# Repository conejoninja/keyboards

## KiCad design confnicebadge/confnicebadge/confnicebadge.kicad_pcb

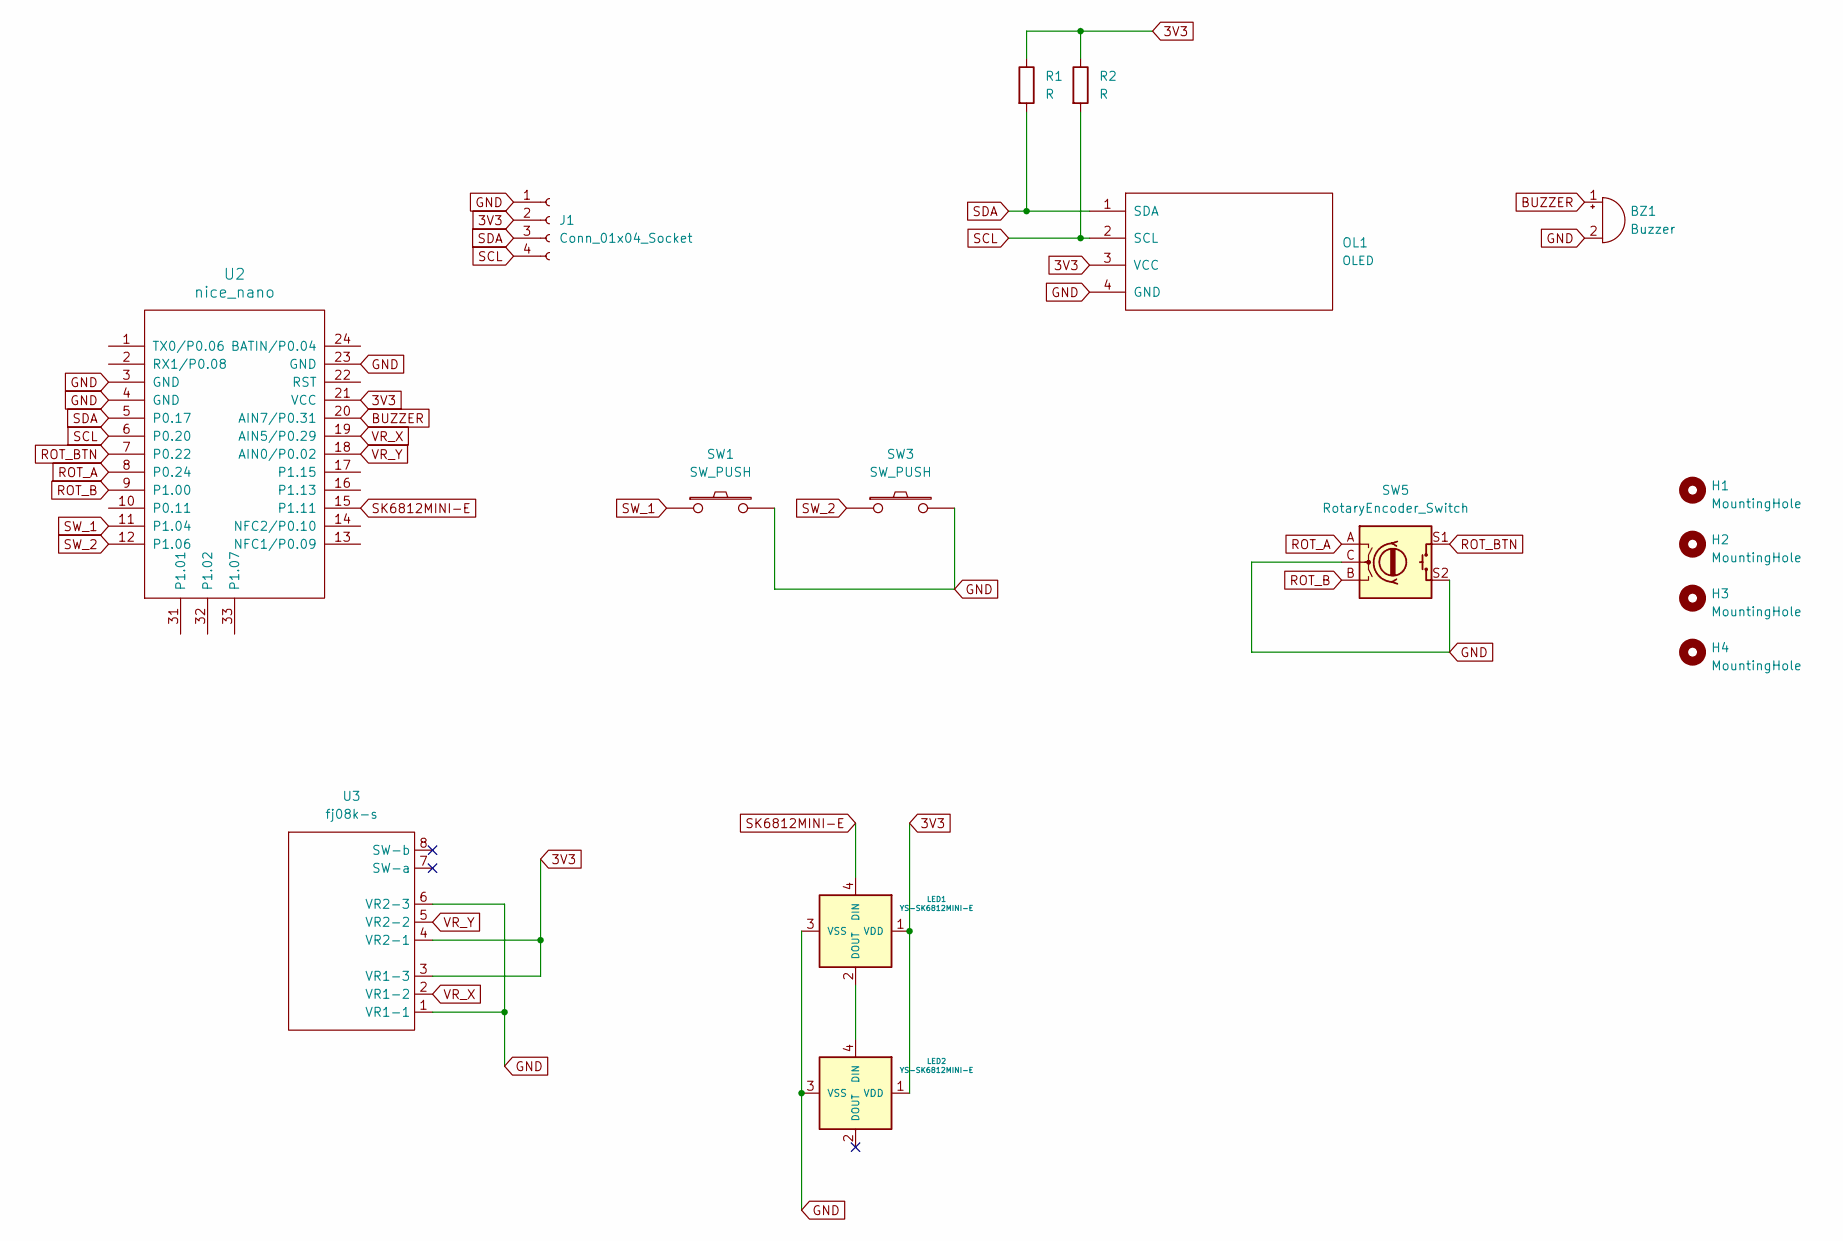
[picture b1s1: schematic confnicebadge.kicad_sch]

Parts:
BZ1: Buzzer; buzzer 5.5mm
H1, H2, H3, H4: MountingHole; M2_HOLE_v2
J1: Conn_01x04_Socket; PinHeader_1x04_P2.54mm_Vertical
LED1, LED2: YS-SK6812MINI-E
OL1: OLED
R1, R2: R; R_Axial_DIN0207_L6.3mm_D2.5mm_P10.16mm_Horizontal
SW1, SW3: SW_PUSH; CherryMX_Hotswap
SW5: RotaryEncoder_Switch; RotaryEncoder_Alps_EC11E-Switch_Vertical_H20mm
U2: nice_nano
U3: fj08k-s; FJ08K-S

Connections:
3V3: J1.2, LED1.1 (VDD), LED2.1 (VDD), OL1.3 (VCC), R1.1, R2.1, U2.21 (VCC), U3.3 (VR1-3), U3.4 (VR2-1)
BUZZER: BZ1.1 (+), U2.20 (AIN7/P0.31)
GND: BZ1.2 (-), J1.1, LED1.3 (VSS), LED2.3 (VSS), OL1.4 (GND), SW1.2, SW3.2, SW5.C, SW5.S2, U2.3 (GND), U2.4 (GND), U2.23 (GND), U3.1 (VR1-1), U3.6 (VR2-3)
unnamed: LED1.2 (DOUT), LED2.4 (DIN)
ROT_A: SW5.A, U2.8 (P0.24)
ROT_B: SW5.B, U2.9 (P1.00)
ROT_BTN: SW5.S1, U2.7 (P0.22)
SCL: J1.4, OL1.2 (SCL), R2.2, U2.6 (P0.20)
SDA: J1.3, OL1.1 (SDA), R1.2, U2.5 (P0.17)
SK6812MINI-E: LED1.4 (DIN), U2.15 (P1.11)
SW_1: SW1.1, U2.11 (P1.04)
SW_2: SW3.1, U2.12 (P1.06)
VR_X: U2.19 (AIN5/P0.29), U3.2 (VR1-2)
VR_Y: U2.18 (AIN0/P0.02), U3.5 (VR2-2)

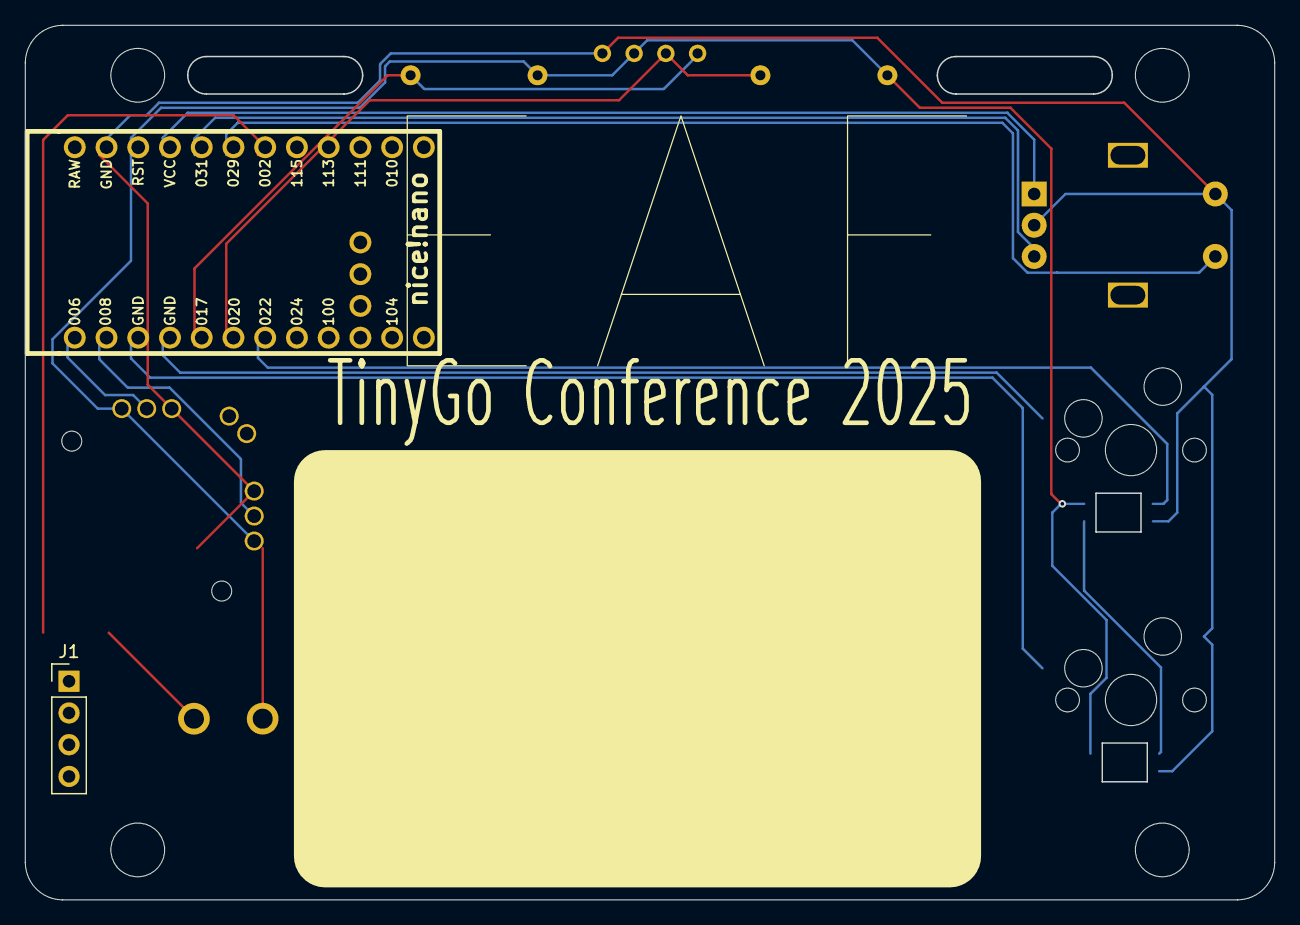
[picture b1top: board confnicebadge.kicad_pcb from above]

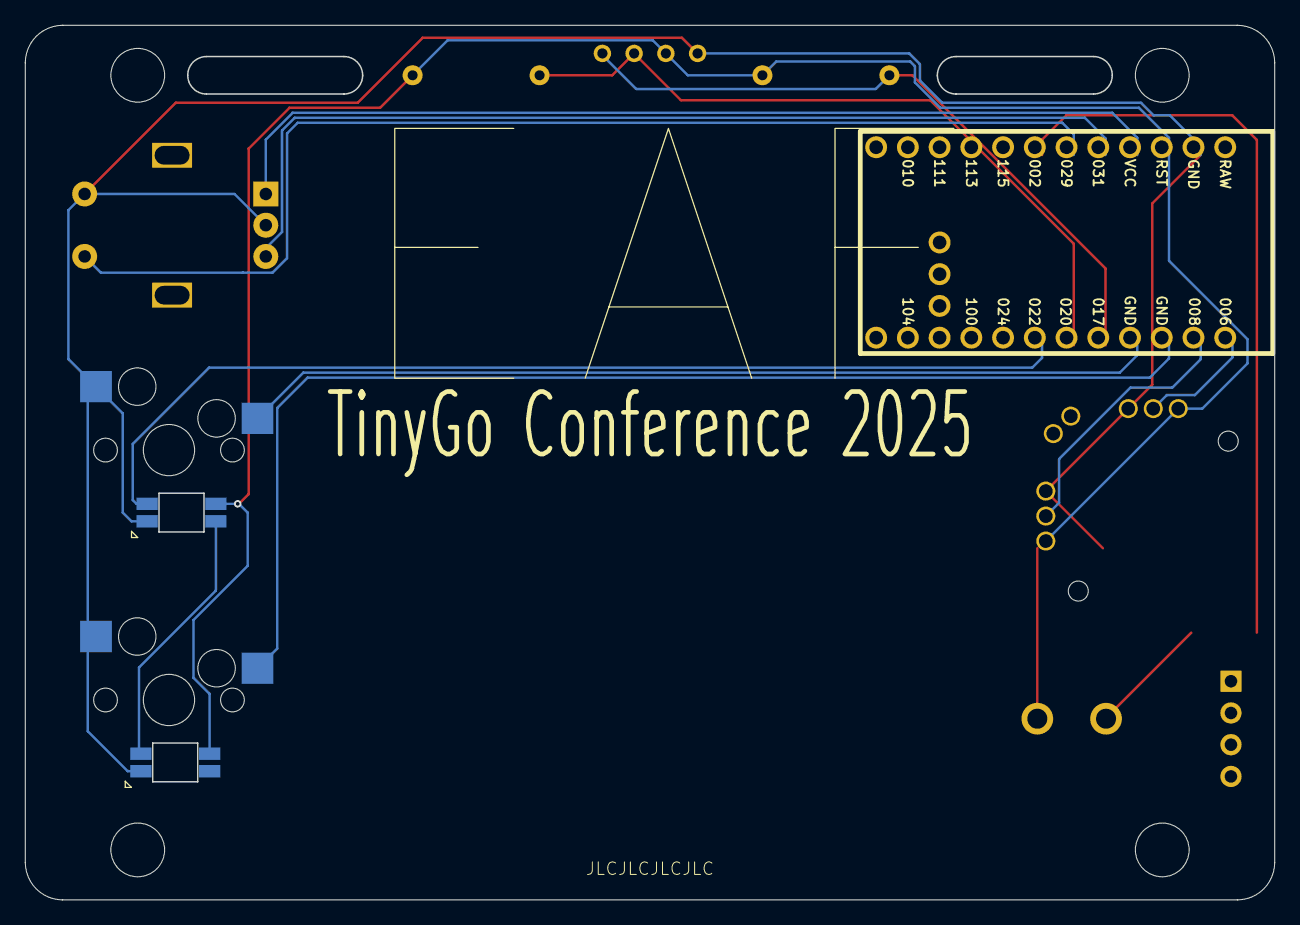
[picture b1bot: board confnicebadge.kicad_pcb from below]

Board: 2 copper layers, 99.9 x 69.9 mm, 18 parts (2 on the bottom side), 14 nets.

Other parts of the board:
SW2, SW2#2: KEY_SWITCH; strap_hole

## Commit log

2026-02-26 opsie
2026-02-26 missing file
